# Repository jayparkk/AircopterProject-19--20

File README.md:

# AircopterProject-19--20
libraries and code for the Aircopter Project
UCLA IEEE '19-'20

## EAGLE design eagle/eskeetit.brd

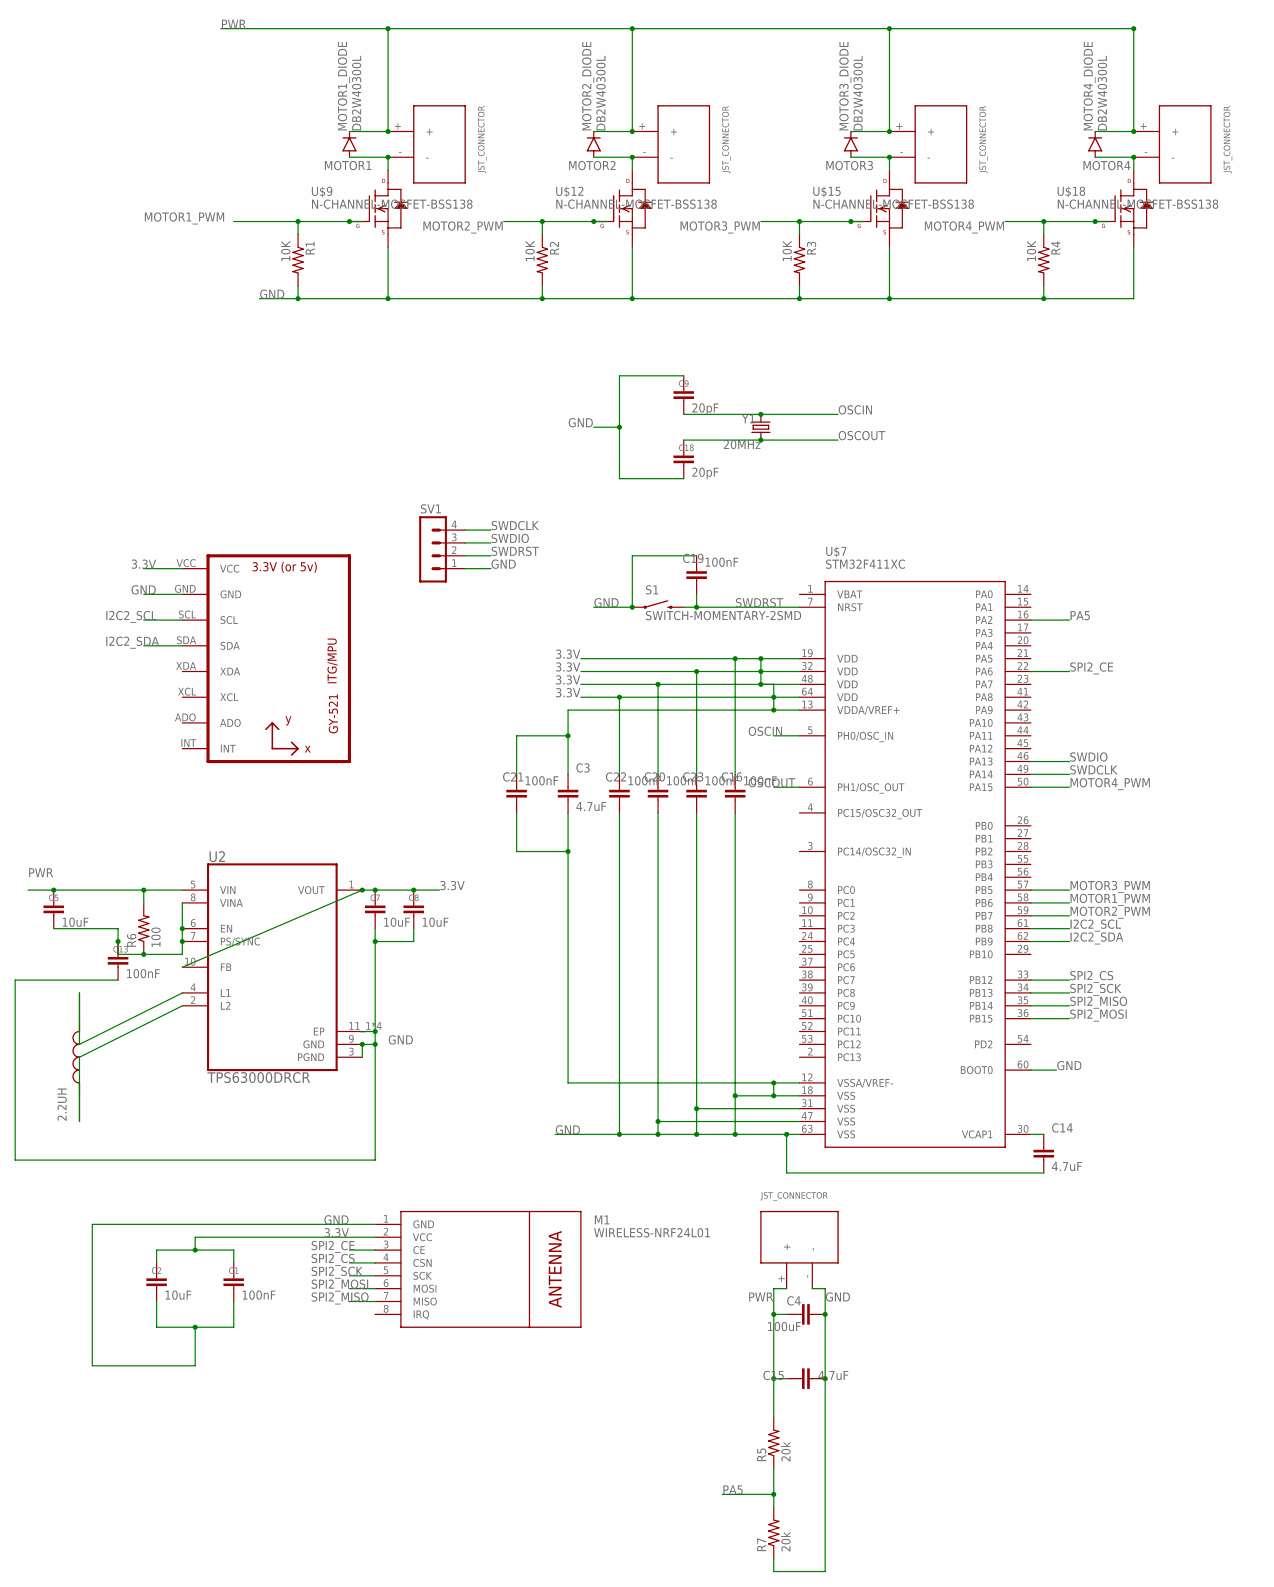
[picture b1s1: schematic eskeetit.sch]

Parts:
2.2UH: 2.2uH; IND_LQH2MCN100K02L
C1, C13, C16, C19, C20, C21, C22, C23: 100nF; RCL_C0603
C2, C5, C7, C8: 10uF; RCL_C0603
C3, C14, C15: 4.7uF; RCL_C0603
C4: 100uF; C1206
C9, C18: 20pF; RCL_C0603
M1: WIRELESS-NRF24L01
MOTOR1: JST_CONNECTOR_FEMALE
MOTOR1_DIODE, MOTOR2_DIODE, MOTOR3_DIODE, MOTOR4_DIODE: DB2W40300L; MINI2-F3-B
R1, R2, R3, R4: 10K; R0603
R5, R7: 20k; R0603
R6: 100; R0603
S1: SWITCH-MOMENTARY-2SMD; TACTILE-SWITCH-SMD
SV1: MA04-1
U1: GY-521MPU6050; GY-521
U2: TPS63000DRCR; CONV_TPS63000DRCR
U$1, U$11, U$14, U$17: JST_CONNECTOR_FEMALE
U$7: STM32F411XC; LQFP64
U$9, U$12, U$15, U$18: N-CHANNEL-MOSFET-BSS138; SOT23-3
Y1: 20MHz; HC49US

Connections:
3.3V: C1.1, C2.1, C3.1, C7.1, C8.1, C16.1, C20.1, C21.1, C22.1, C23.1, M1.2 (VCC), U1.VCC, U2.1 (VOUT), U2.10 (FB), U$7.13 (VDDA/VREF+), U$7.19 (VDD), U$7.32 (VDD), U$7.48 (VDD), U$7.64 (VDD)
GND: C1.2, C2.2, C3.2, C4.1, C7.2, C8.2, C9.1, C13.2, C14.2, C15.2, C16.2, C18.2, C19.1, C20.2, C21.2, C22.2, C23.2, M1.1 (GND), R1.2, R2.2, R3.2, R4.2, R7.1, S1.1, SV1.1, U1.GND, U2.3 (PGND), U2.9 (GND), U2.11_1 (EP), U2.11_2 (EP), U2.11_3 (EP), U2.11_4 (EP), U$1.-, U$7.12 (VSSA/VREF-), U$7.18 (VSS), U$7.31 (VSS), U$7.47 (VSS), U$7.60 (BOOT0), U$7.63 (VSS), U$9.2 (S), U$12.2 (S), U$15.2 (S), U$18.2 (S)
I2C2_SCL: U1.SCL, U$7.61 (PB8)
I2C2_SDA: U1.SDA, U$7.62 (PB9)
MOTOR1: MOTOR1.-, MOTOR1_DIODE.POS (PPIN), U$9.3 (D)
MOTOR1_PWM: R1.1, U$7.58 (PB6), U$9.1 (G)
MOTOR2: MOTOR2_DIODE.POS (PPIN), U$11.-, U$12.3 (D)
MOTOR2_PWM: R2.1, U$7.59 (PB7), U$12.1 (G)
MOTOR3: MOTOR3_DIODE.POS (PPIN), U$14.-, U$15.3 (D)
MOTOR3_PWM: R3.1, U$7.57 (PB5), U$15.1 (G)
MOTOR4: MOTOR4_DIODE.POS (PPIN), U$17.-, U$18.3 (D)
MOTOR4_PWM: R4.1, U$7.50 (PA15), U$18.1 (G)
unnamed: 2.2UH.2, U2.4 (L1)
unnamed: 2.2UH.1, U2.2 (L2)
unnamed: C5.2, C13.1, R6.1, U2.6 (EN), U2.7 (PS/SYNC), U2.8 (VINA)
unnamed: C14.1, U$7.30 (VCAP1)
OSCIN: C9.2, U$7.5 (PH0/OSC_IN), Y1.2
OSCOUT: C18.1, U$7.6 (PH1/OSC_OUT), Y1.1
PA5: R5.1, R7.2, U$7.16 (PA2)
PWR: C4.2, C5.1, C15.1, MOTOR1.+, MOTOR1_DIODE.NEG (GPIN), MOTOR2_DIODE.NEG (GPIN), MOTOR3_DIODE.NEG (GPIN), MOTOR4_DIODE.NEG (GPIN), R5.2, R6.2, U2.5 (VIN), U$1.+, U$11.+, U$14.+, U$17.+
SPI2_CE: M1.3 (CE), U$7.22 (PA6)
SPI2_CS: M1.4 (CSN), U$7.33 (PB12)
SPI2_MISO: M1.7 (MISO), U$7.35 (PB14)
SPI2_MOSI: M1.6 (MOSI), U$7.36 (PB15)
SPI2_SCK: M1.5 (SCK), U$7.34 (PB13)
SWDCLK: SV1.4, U$7.49 (PA14)
SWDIO: SV1.3, U$7.46 (PA13)
SWDRST: C19.2, S1.3 (2), SV1.2, U$7.7 (NRST)

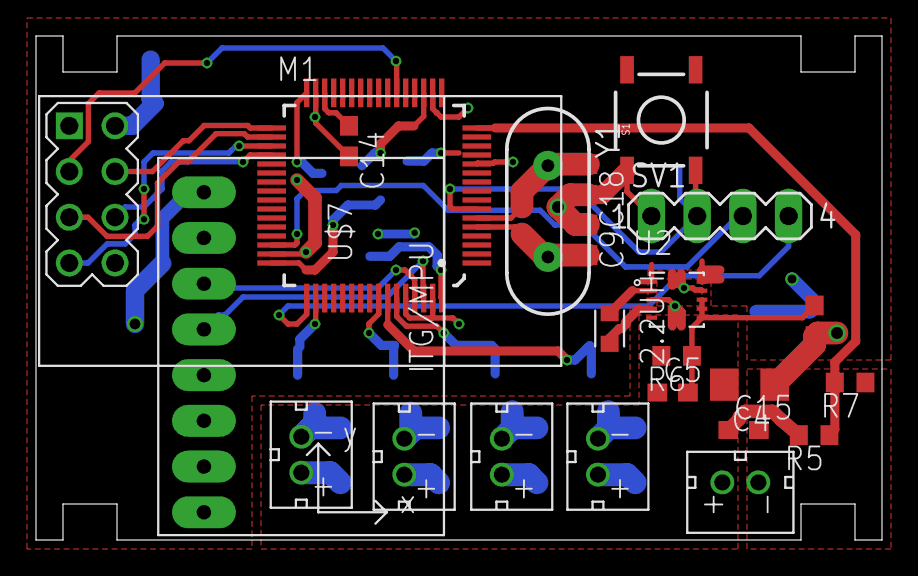
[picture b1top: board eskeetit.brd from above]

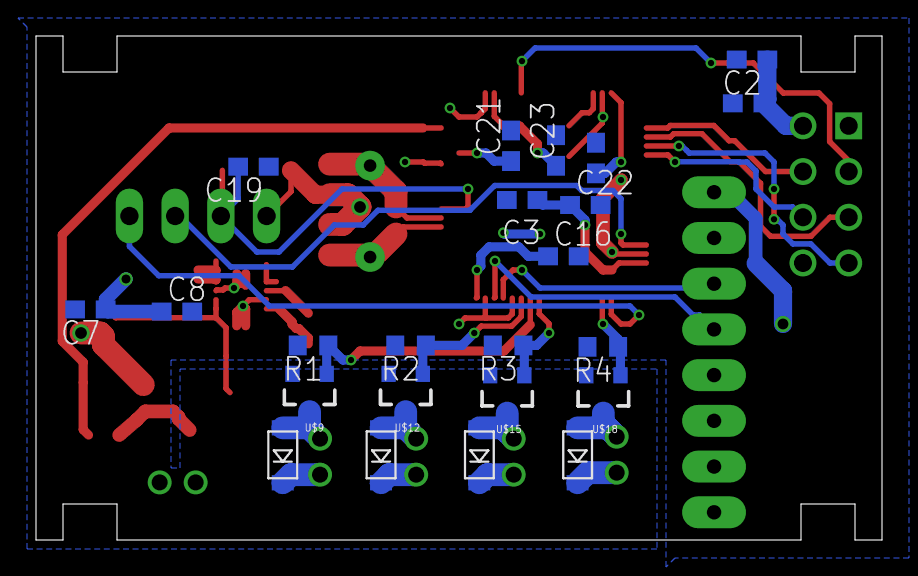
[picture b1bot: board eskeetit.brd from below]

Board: 2 copper layers, 47.0 x 28.0 mm, 46 parts (23 on the bottom side), 28 nets.

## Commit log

2020-02-28 nRF24L01P library
2020-02-28 schamatic and board
2020-02-28 motor pwm 6mil->20mil to reduce parasitic elements
2020-02-28 improved trace angles, top layer motor pwm 12mil->20mil
2020-02-28 top layer motor pwm 20mil->50mil
2020-02-28 deleted extra brd files
2020-03-04 changed PA5 to 20 mils, fixed some bottlenecks
2020-03-08 PCB Notes, first remote revisions (Vaibhav)
2020-03-08 fixed drc errors
2020-03-08 fixed changes in the remote design review
2020-03-08 moved capacitors near the JST Connectors
2020-03-08 fixed some bottlenecks
2020-03-09 more bottleneck fixes
2020-03-11 leads are roasting us and we are trying to fix
2020-03-12 final revision god I hope this board works
2020-03-16 this is a test commit
